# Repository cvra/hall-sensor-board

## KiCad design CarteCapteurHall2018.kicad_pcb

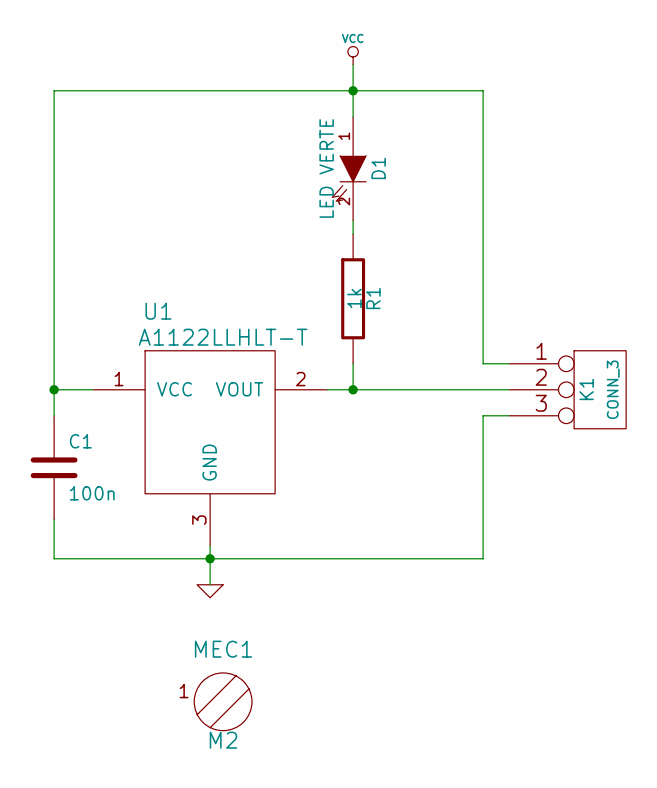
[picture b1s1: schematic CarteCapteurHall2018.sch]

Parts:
C1: 100n; _0603
D1: LED VERTE; _0603
K1: CONN_3; Molex_PicoBlade_53398-0371_03x1.25mm_Straight
MEC1: M2; MountingHole_2.2mm_M2
R1: 1k; _0603
U1: A1122LLHLT-T; SOT-23W

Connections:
GND: C1.2, K1.3, U1.3 (GND)
unnamed: D1.2 (K), R1.1
unnamed: K1.2 (PM), R1.2, U1.2 (VOUT)
VCC: C1.1, D1.1 (A), K1.1, U1.1 (VCC)

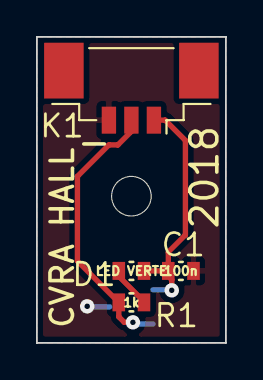
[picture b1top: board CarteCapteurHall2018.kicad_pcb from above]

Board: 2 copper layers, 10.5 x 17.0 mm, 6 parts (1 on the bottom side), 4 nets.

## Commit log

2020-03-16 import hall sensor files
